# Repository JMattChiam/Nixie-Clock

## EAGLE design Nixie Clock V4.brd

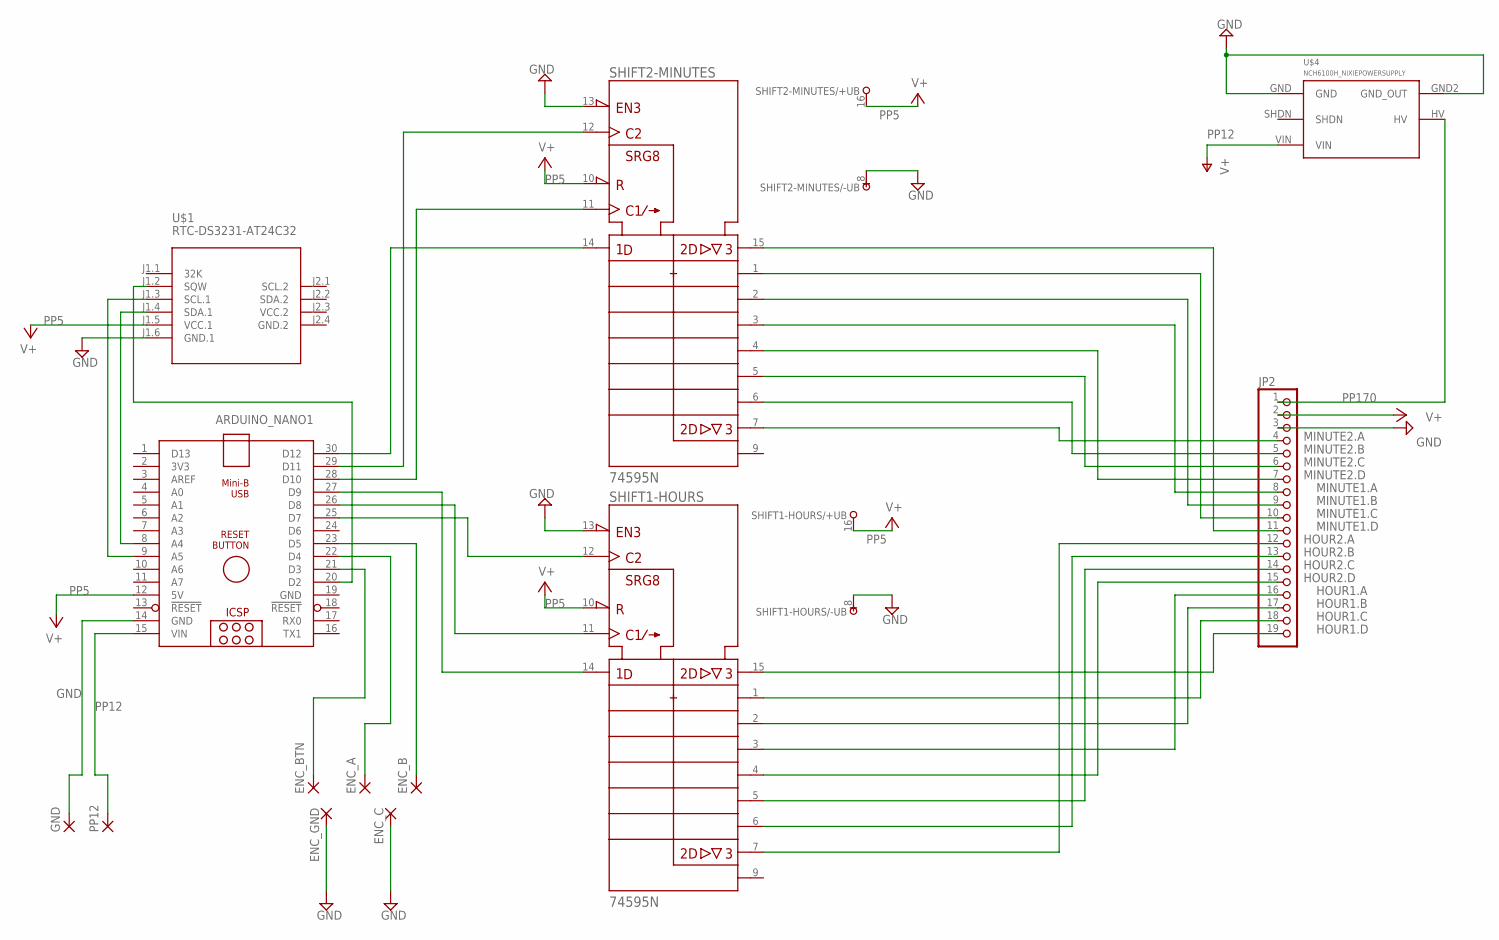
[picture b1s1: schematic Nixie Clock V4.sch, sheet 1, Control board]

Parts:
ARDUINO_NANO1: ARDUINO_NANO
ENC_A: 2,54/1,0
ENC_B: 2,54/1,0
ENC_BTN: 2,54/1,0
ENC_C: 2,54/1,0
ENC_GND: 2,54/1,0
GND: 2,54/1,0
JP2: PINHD-1X19; 1X19
PP12: 2,54/1,0
SHIFT1-HOURS, SHIFT2-MINUTES: 74595N; DIL16
U$1: RTC-DS3231-AT24C32
U$4: NCH6100H_NIXIEPOWERSUPPLY; NCH6100HV_NIXIEPOWERSUPPLY

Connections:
GND: ARDUINO_NANO1.14 (GND), ARDUINO_NANO1.19 (GND), ENC_C.1, ENC_GND.1, GND.1, JP2.3, SHIFT1-HOURS.8 (-UB), SHIFT1-HOURS.13 (!G), SHIFT2-MINUTES.8 (-UB), SHIFT2-MINUTES.13 (!G), U$1.J1.6 (GND.1), U$4.GND, U$4.GND2 (GND_OUT)
GND.2: U$1.J2.4 (GND.2)
HOUR1.A: JP2.16, SHIFT1-HOURS.3 (QD)
HOUR1.B: JP2.17, SHIFT1-HOURS.2 (QC)
HOUR1.C: JP2.18, SHIFT1-HOURS.1 (QB)
HOUR1.D: JP2.19, SHIFT1-HOURS.15 (QA)
HOUR2.A: JP2.12, SHIFT1-HOURS.7 (QH)
HOUR2.B: JP2.13, SHIFT1-HOURS.6 (QG)
HOUR2.C: JP2.14, SHIFT1-HOURS.5 (QF)
HOUR2.D: JP2.15, SHIFT1-HOURS.4 (QE)
MINUTE1.A: JP2.8, SHIFT2-MINUTES.3 (QD)
MINUTE1.B: JP2.9, SHIFT2-MINUTES.2 (QC)
MINUTE1.C: JP2.10, SHIFT2-MINUTES.1 (QB)
MINUTE1.D: JP2.11, SHIFT2-MINUTES.15 (QA)
MINUTE2.A: JP2.4, SHIFT2-MINUTES.7 (QH)
MINUTE2.B: JP2.5, SHIFT2-MINUTES.6 (QG)
MINUTE2.C: JP2.6, SHIFT2-MINUTES.5 (QF)
MINUTE2.D: JP2.7, SHIFT2-MINUTES.4 (QE)
unnamed: ARDUINO_NANO1.8 (A4), U$1.J1.4 (SDA.1)
unnamed: ARDUINO_NANO1.9 (A5), U$1.J1.3 (SCL.1)
unnamed: ARDUINO_NANO1.30 (D12), SHIFT2-MINUTES.14 (SER)
unnamed: ARDUINO_NANO1.29 (D11), SHIFT2-MINUTES.12 (RCK)
unnamed: ARDUINO_NANO1.28 (D10), SHIFT2-MINUTES.11 (SRCK)
unnamed: ARDUINO_NANO1.22 (D4), ENC_A.1
unnamed: ARDUINO_NANO1.26 (D8), SHIFT1-HOURS.11 (SRCK)
unnamed: ARDUINO_NANO1.25 (D7), SHIFT1-HOURS.12 (RCK)
unnamed: ARDUINO_NANO1.23 (D5), ENC_B.1
unnamed: ARDUINO_NANO1.21 (D3), ENC_BTN.1
unnamed: ARDUINO_NANO1.20 (D2), U$1.J1.2 (SQW)
PP5: ARDUINO_NANO1.12 (5V), JP2.2, SHIFT1-HOURS.10 (!SRCLR), SHIFT1-HOURS.16 (+UB), SHIFT2-MINUTES.10 (!SRCLR), SHIFT2-MINUTES.16 (+UB), U$1.J1.5 (VCC.1)
PP12: ARDUINO_NANO1.15 (VIN), PP12.1, U$4.VIN
PP170: JP2.1, U$4.HV
SERIAL-IN: ARDUINO_NANO1.27 (D9), SHIFT1-HOURS.14 (SER)
VCC.2: U$1.J2.3 (VCC.2)

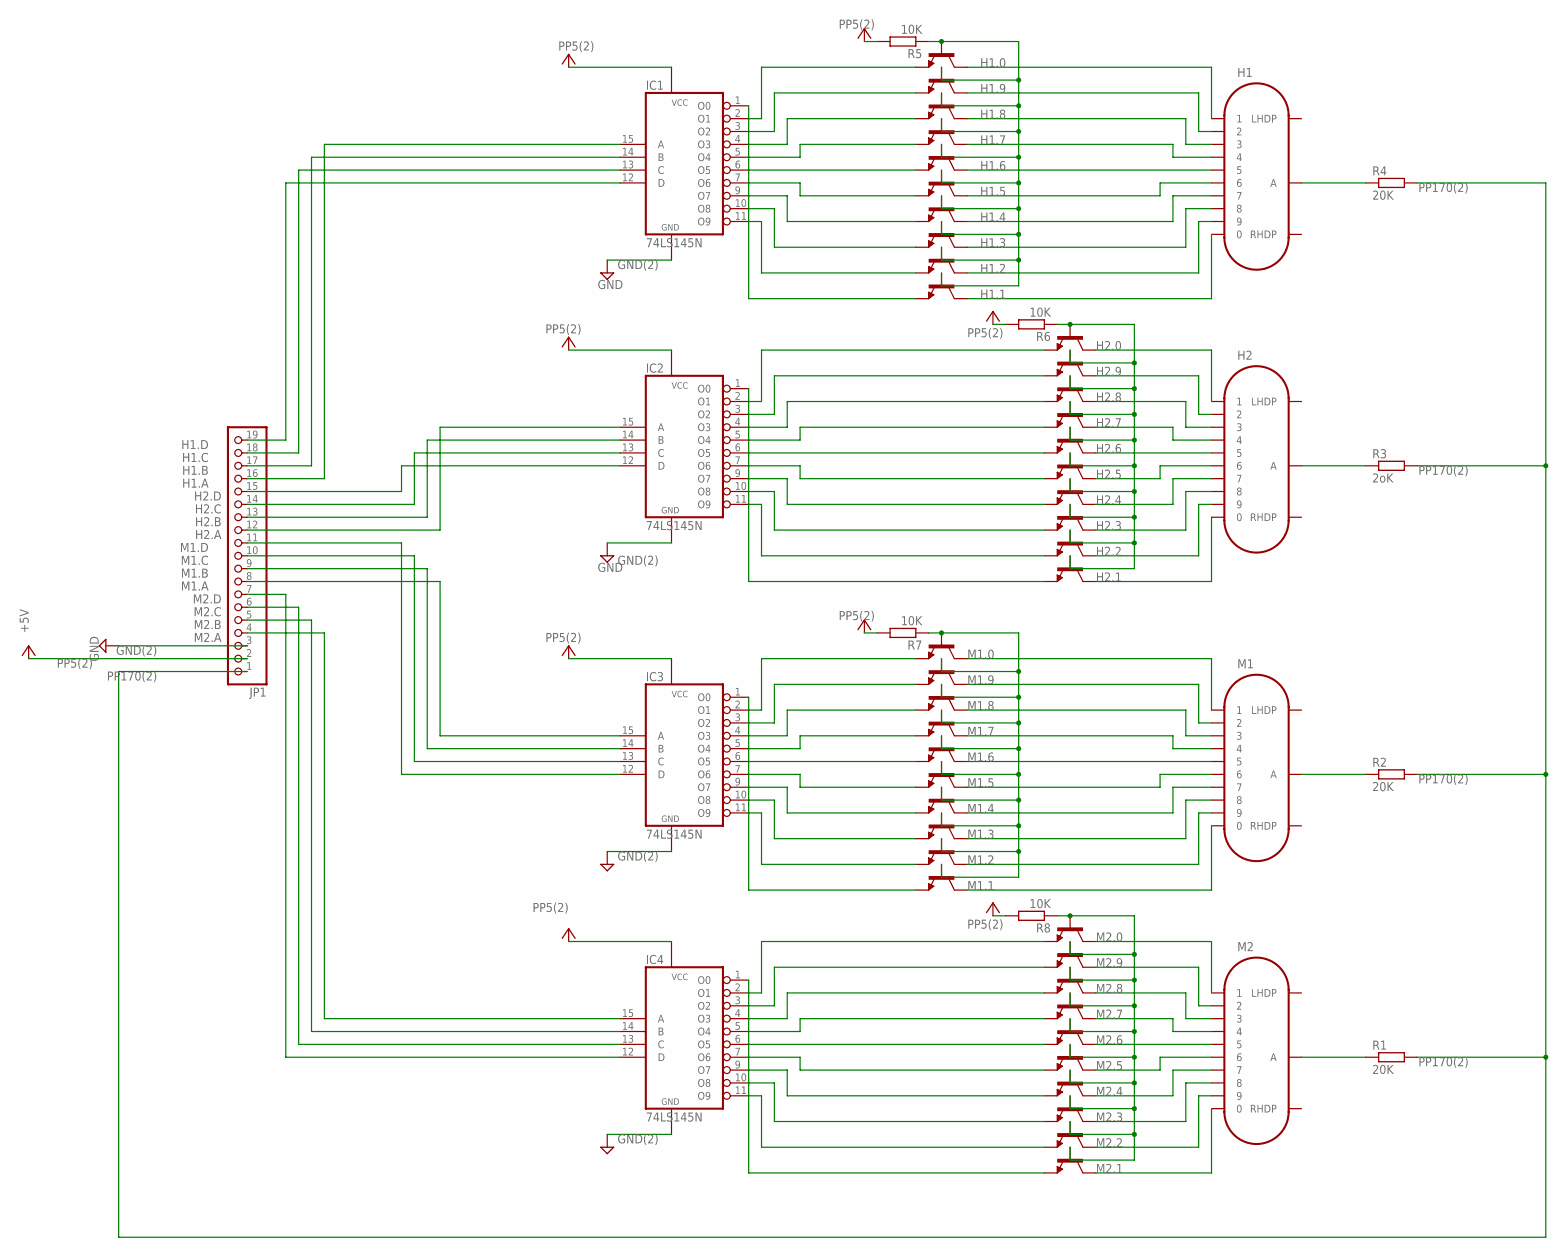
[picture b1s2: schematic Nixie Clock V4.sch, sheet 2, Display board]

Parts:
H1, H2: IN-14
H1.0, H1.1, H1.2, H1.3, H1.4, H1.5, H1.6, H1.7, H1.8, H1.9, H2.0, H2.1, H2.2, H2.3, H2.4, H2.5, H2.6, H2.7, H2.8, H2.9: MPSA42-NPN-TO92-EBC; TO92-EBC
IC1, IC2, IC3, IC4: 74LS145N; DIL16
JP1: PINHD-1X19; 1X19
M1, M2: IN-14
M1.0, M1.1, M1.2, M1.3, M1.4, M1.5, M1.6, M1.7, M1.8, M1.9, M2.0, M2.1, M2.2, M2.3, M2.4, M2.5, M2.6, M2.7, M2.8, M2.9: MPSA42-NPN-TO92-EBC; TO92-EBC
R1, R2, R4: 20K; 0411/12
R3: 2oK; 0411/12
R5, R6, R7, R8: 10K; 0411/12

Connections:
GND(2): IC1.8 (GND), IC2.8 (GND), IC3.8 (GND), IC4.8 (GND), JP1.3
H1.A: IC1.15 (A), JP1.16
H1.B: IC1.14 (B), JP1.17
H1.C: IC1.13 (C), JP1.18
H1.D: IC1.12 (D), JP1.19
H2.A: IC2.15 (A), JP1.12
H2.B: IC2.14 (B), JP1.13
H2.C: IC2.13 (C), JP1.14
H2.D: IC2.12 (D), JP1.15
M1.4: M1.0.B, M1.1.B, M1.2.B, M1.3.B, M1.4.B, M1.5.B, M1.6.B, M1.7.B, M1.8.B, M1.9.B, R7.1
M1.A: IC3.15 (A), JP1.8
M1.B: IC3.14 (B), JP1.9
M1.C: IC3.13 (C), JP1.10
M1.D: IC3.12 (D), JP1.11
M2.4: M2.0.B, M2.1.B, M2.2.B, M2.3.B, M2.4.B, M2.5.B, M2.6.B, M2.7.B, M2.8.B, M2.9.B, R8.1
M2.A: IC4.15 (A), JP1.4
M2.B: IC4.14 (B), JP1.5
M2.C: IC4.13 (C), JP1.6
M2.D: IC4.12 (D), JP1.7
unnamed: H1.0.B, H1.1.B, H1.2.B, H1.3.B, H1.4.B, H1.5.B, H1.6.B, H1.7.B, H1.8.B, H1.9.B, R5.1
unnamed: H2.0.B, H2.1.B, H2.2.B, H2.3.B, H2.4.B, H2.5.B, H2.6.B, H2.7.B, H2.8.B, H2.9.B, R6.1
unnamed: M2.1, M2.0.C
unnamed: M2.2, M2.9.C
unnamed: M2.3, M2.8.C
unnamed: M2.4, M2.7.C
unnamed: M2.0, M2.1.C
unnamed: M2.9, M2.2.C
unnamed: M2.8, M2.3.C
unnamed: M2.7, M2.4.C
unnamed: M2.6, M2.5.C
unnamed: M2.5, M2.6.C
unnamed: M1.5, M1.6.C
unnamed: M1.1, M1.0.C
unnamed: M1.2, M1.9.C
unnamed: M1.3, M1.8.C
unnamed: M1.4, M1.7.C
unnamed: M1.0, M1.1.C
unnamed: M1.9, M1.2.C
unnamed: M1.8, M1.3.C
unnamed: M1.7, M1.4.C
unnamed: M1.6, M1.5.C
unnamed: H2.0, H2.1.C
unnamed: H2.9, H2.2.C
unnamed: H2.8, H2.3.C
unnamed: H2.1, H2.0.C
unnamed: H2.2, H2.9.C
unnamed: H2.3, H2.8.C
unnamed: H2.7, H2.4.C
unnamed: H2.6, H2.5.C
unnamed: H2.4, H2.7.C
unnamed: H2.5, H2.6.C
unnamed: H1.1, H1.0.C
unnamed: H1.2, H1.9.C
unnamed: H1.3, H1.8.C
unnamed: H1.4, H1.7.C
unnamed: H1.5, H1.6.C
unnamed: H1.0, H1.1.C
unnamed: H1.9, H1.2.C
unnamed: H1.8, H1.3.C
unnamed: H1.7, H1.4.C
unnamed: H1.6, H1.5.C
unnamed: IC4.2 (O1), M2.0.E
unnamed: IC4.3 (O2), M2.9.E
unnamed: IC4.4 (O3), M2.8.E
unnamed: IC4.5 (O4), M2.7.E
unnamed: IC4.6 (O5), M2.6.E
unnamed: IC4.7 (O6), M2.5.E
unnamed: IC4.9 (O7), M2.4.E
unnamed: IC4.10 (O8), M2.3.E
unnamed: IC4.11 (O9), M2.2.E
unnamed: IC4.1 (O0), M2.1.E
unnamed: IC3.6 (O5), M1.6.E
unnamed: H1.6.E, IC1.6 (O5)
unnamed: H2.6.E, IC2.6 (O5)
unnamed: M2.A, R1.1
unnamed: M1.A, R2.1
unnamed: H2.A, R3.1
unnamed: H1.A, R4.1
unnamed: IC3.2 (O1), M1.0.E
unnamed: IC3.3 (O2), M1.9.E
unnamed: IC3.4 (O3), M1.8.E
unnamed: IC3.5 (O4), M1.7.E
unnamed: IC3.7 (O6), M1.5.E
unnamed: IC3.9 (O7), M1.4.E
unnamed: IC3.10 (O8), M1.3.E
unnamed: IC3.11 (O9), M1.2.E
unnamed: IC3.1 (O0), M1.1.E
unnamed: H2.0.E, IC2.2 (O1)
unnamed: H2.9.E, IC2.3 (O2)
unnamed: H2.8.E, IC2.4 (O3)
unnamed: H2.7.E, IC2.5 (O4)
unnamed: H2.5.E, IC2.7 (O6)
unnamed: H2.4.E, IC2.9 (O7)
unnamed: H2.3.E, IC2.10 (O8)
unnamed: H2.2.E, IC2.11 (O9)
unnamed: H2.1.E, IC2.1 (O0)
unnamed: H1.0.E, IC1.2 (O1)
unnamed: H1.9.E, IC1.3 (O2)
unnamed: H1.8.E, IC1.4 (O3)
unnamed: H1.7.E, IC1.5 (O4)
unnamed: H1.5.E, IC1.7 (O6)
unnamed: H1.4.E, IC1.9 (O7)
unnamed: H1.3.E, IC1.10 (O8)
unnamed: H1.2.E, IC1.11 (O9)
unnamed: H1.1.E, IC1.1 (O0)
PP5(2): IC1.16 (VCC), IC2.16 (VCC), IC3.16 (VCC), IC4.16 (VCC), JP1.2, R5.2, R6.2, R7.2, R8.2
PP170(2): JP1.1, R1.2, R2.2, R3.2, R4.2

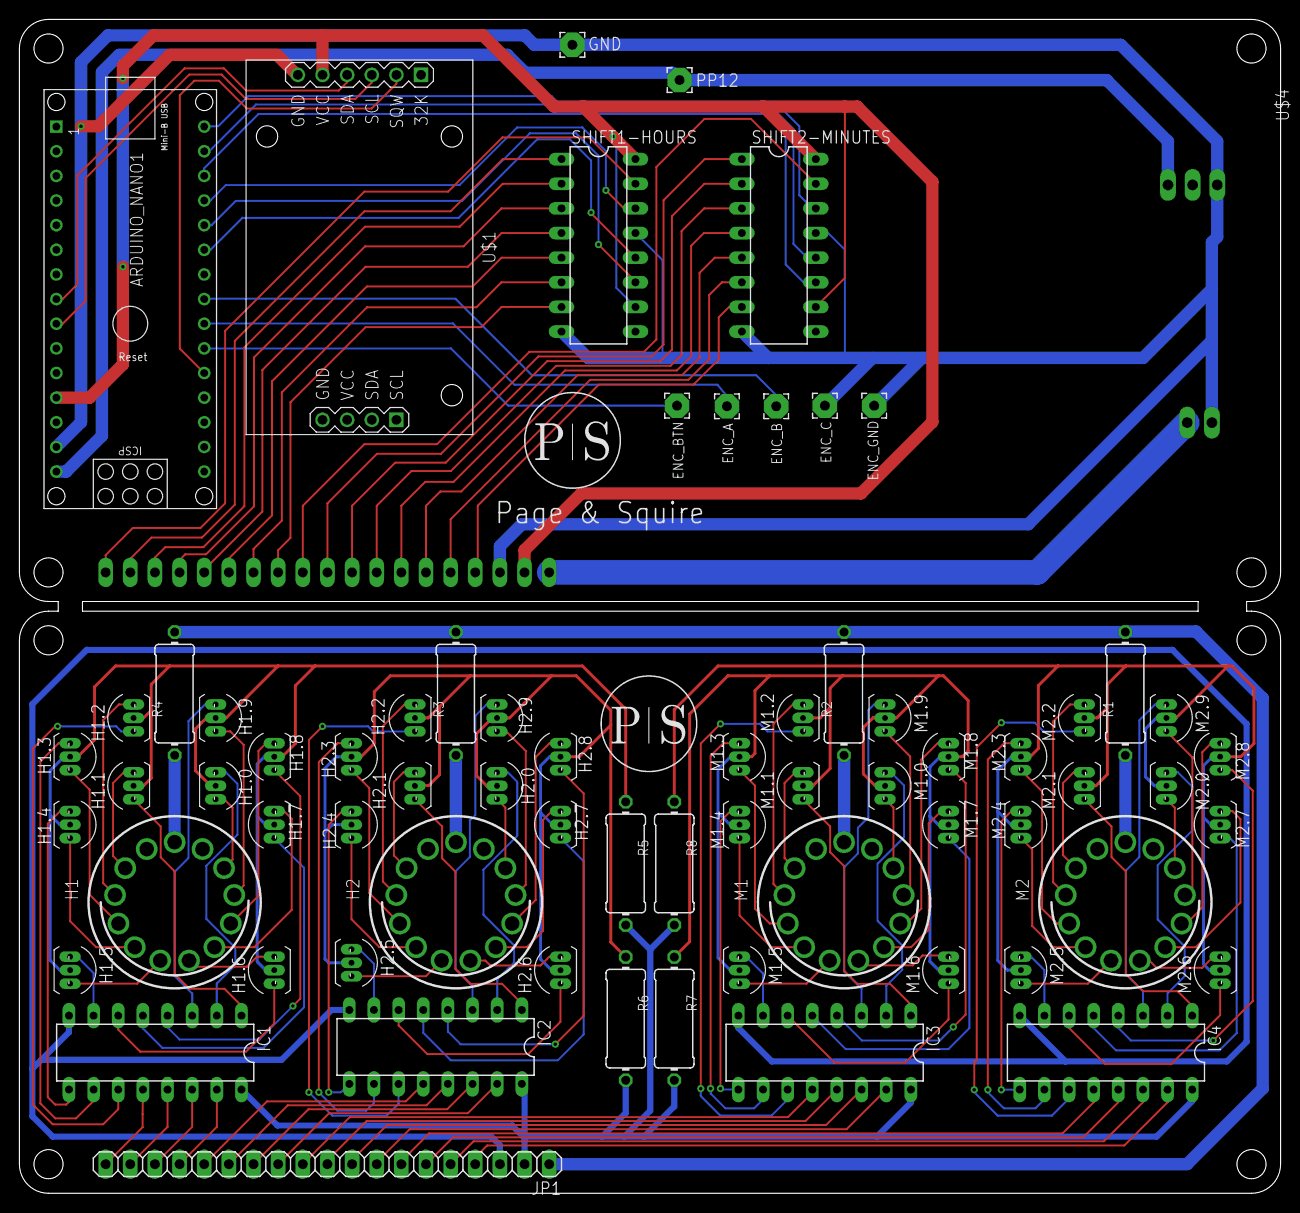
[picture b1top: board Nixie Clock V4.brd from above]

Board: 2 copper layers, 130.0 x 121.0 mm, 70 parts (1 on the bottom side), 139 nets.

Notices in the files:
parts and their libraries:
diy-modules: Released under the Creative Commons Attribution 4.0 International License: http://creativecommons.org/licenses/by/4.0
